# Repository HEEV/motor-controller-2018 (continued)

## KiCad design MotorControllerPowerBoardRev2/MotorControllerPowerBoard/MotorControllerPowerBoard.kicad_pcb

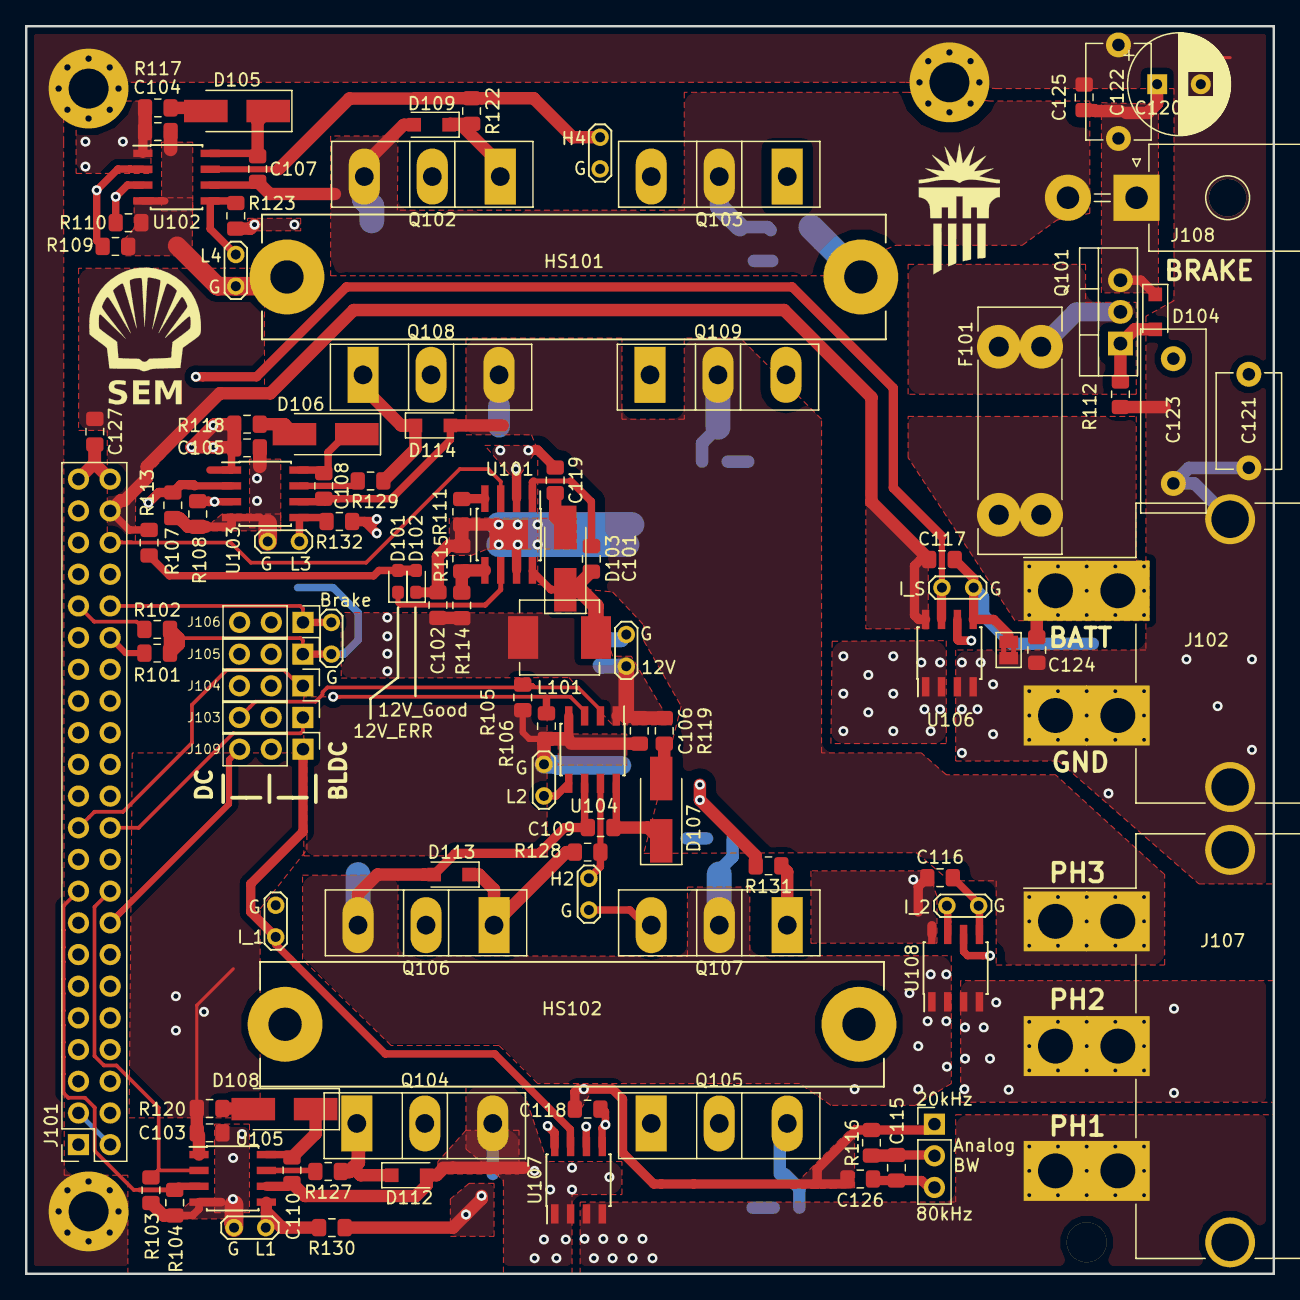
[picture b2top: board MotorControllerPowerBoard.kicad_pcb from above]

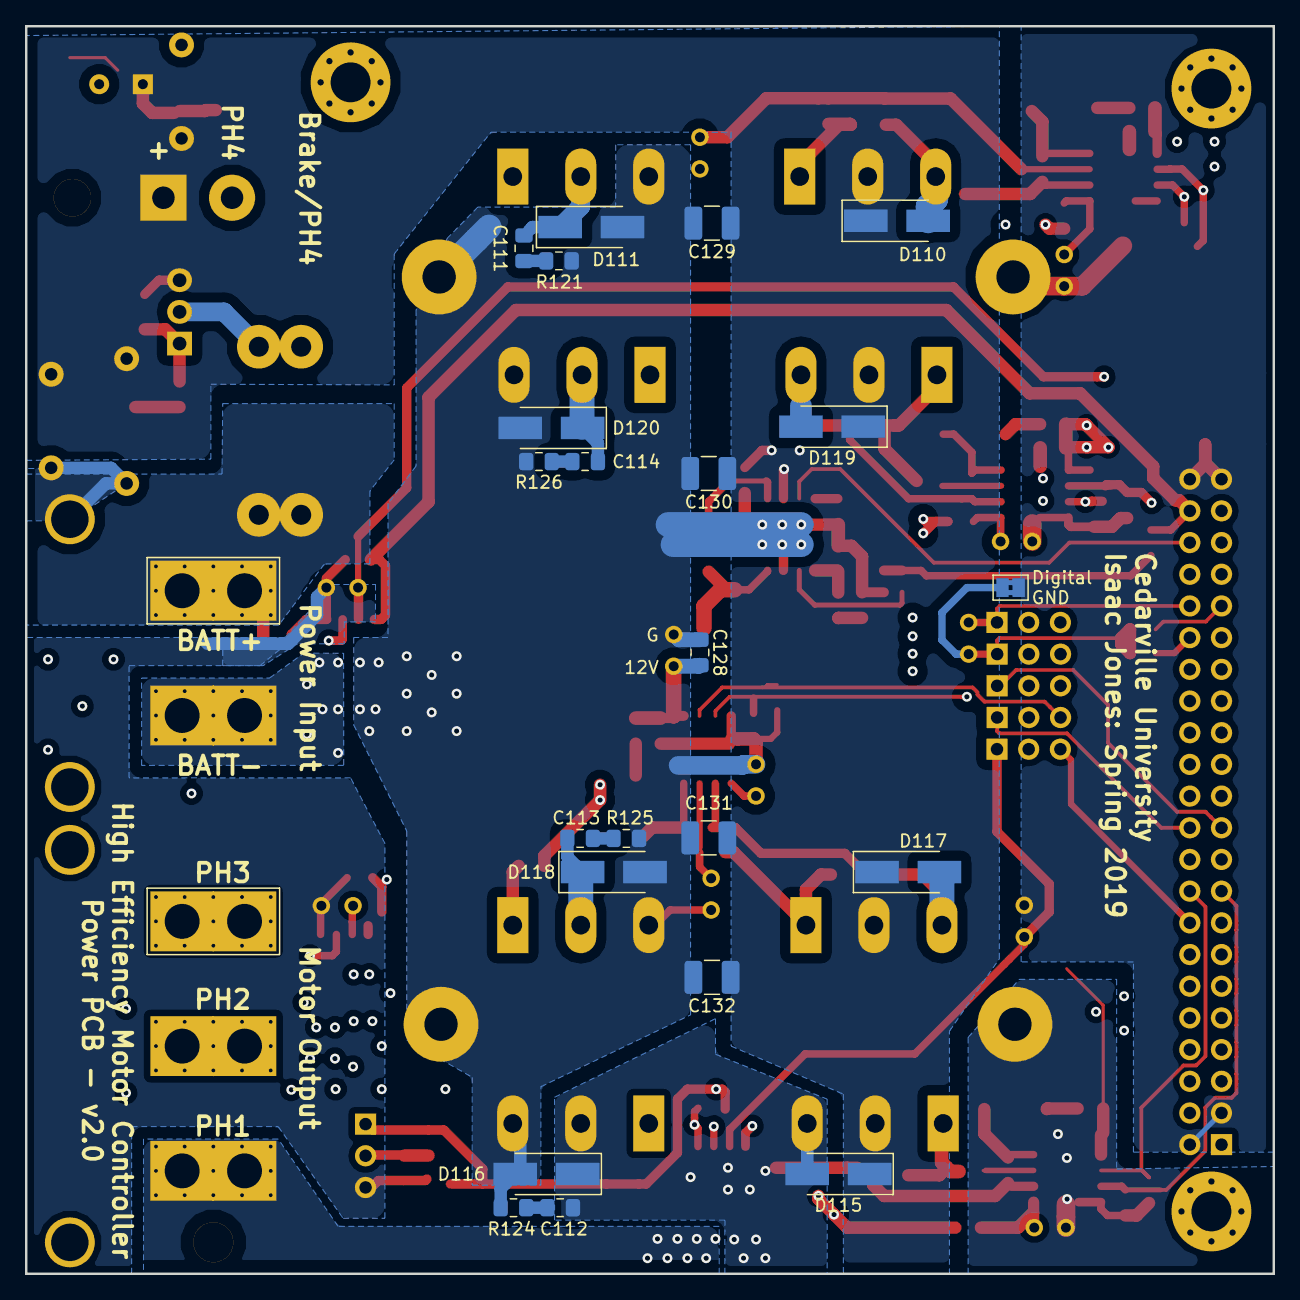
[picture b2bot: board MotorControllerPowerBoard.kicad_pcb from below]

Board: 4 copper layers, 100.0 x 100.0 mm, 130 parts (22 on the bottom side), 69 nets.

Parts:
C101: 0.1u/>16V; C_0805_2012Metric_Pad1.15x1.40mm_HandSolder
C102, C103, C104, C105, C106, C116, C117, C118, C119, C128: 1u; C_0805_2012Metric_Pad1.15x1.40mm_HandSolder
C107, C108, C109, C110: 0.1u; C_0805_2012Metric_Pad1.15x1.40mm_HandSolder
C111, C112, C113, C114: 10n; C_0805_2012Metric_Pad1.15x1.40mm_HandSolder
C115, C124, C125, C126, C127: opt; C_0805_2012Metric_Pad1.15x1.40mm_HandSolder
C120: opt; CP_Radial_D8.0mm_P3.50mm
C121, C122: opt; C_Disc_D7.5mm_W5.0mm_P7.50mm
C123: opt; C_Disc_D14.5mm_W5.0mm_P10.00mm
C129, C130, C131, C132: 4u7; C_1210_3225Metric_Pad1.42x2.65mm_HandSolder
D101: LED_RED; LED_0603_1608Metric_Pad1.05x0.95mm_HandSolder
D102: LED_GRN; LED_0603_1608Metric_Pad1.05x0.95mm_HandSolder
D103, D105, D106, D107, D108, D110, D111, D115, D116, D117, D118, D119, D120: SK56A; D_SMA_Handsoldering
D104, D109, D112, D113, D114: Zener_15V; D_SOD-123F
F101: Fuse/Bypass; Keystone_Blade_Fuseholder_3557-2
GNDPWR: MountingHole_3.2mm_M3
GNDPWR#2: MountingHole_3.2mm_M3_Pad_Via
HS101, HS102: CR401; Heatsink_CR401x50
J101: Trinamic Bridge; PinSocket_2x22_P2.54mm_Vertical
J102: Battery; Molex_Mini-Fit_Sr_42820-22XX_1x02_P10.00mm_Horizontal_Therm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
J103: P3H; PinHeader_1x03_P2.54mm_Vertical
J104: P3L; PinHeader_1x03_P2.54mm_Vertical
J105: P4H; PinHeader_1x03_P2.54mm_Vertical
J106: P4L; PinHeader_1x03_P2.54mm_Vertical
J107: Motor_BLDC; Molex_Mini-Fit_Sr_42820-32XX_1x03_P10.00mm_Horizontal_Therm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
J108: Brake; Molex_Mega-Fit_76825-0002_2x01_P5.70mm_Horizontal
J109: I_Sel; PinHeader_1x03_P2.54mm_Vertical
J110: BW_SEL; PinHeader_1x03_P2.54mm_Vertical
JP101, JP102: Jumper_NC_Small; SolderJumper-2_P1.3mm_Bridged2Bar_Pad1.0x1.5mm
L101: ETQP3M220KVN; PCC-M0630M-LP
Q101: SUP90P06-09L; TO-220-3_Vertical
Q102, Q103, Q104, Q105, Q106, Q107, Q108, Q109: IRFP3306; TO-247-3_Vertical
R101, R102, R103, R104, R105, R106, R107, R108, R109, R110, R112, R115, R116: 10k; R_0805_2012Metric_Pad1.15x1.40mm_HandSolder
R111: 22k; R_0805_2012Metric_Pad1.15x1.40mm_HandSolder
R113: 1k5; R_0805_2012Metric_Pad1.15x1.40mm_HandSolder
R114: 150k; R_0805_2012Metric_Pad1.15x1.40mm_HandSolder
R117: small; R_0805_2012Metric_Pad1.15x1.40mm_HandSolder
R118, R119, R120, R122, R123, R127, R128, R129, R130, R131, R132: R; R_0805_2012Metric_Pad1.15x1.40mm_HandSolder
R121, R124, R125, R126: 1R; R_0805_2012Metric_Pad1.15x1.40mm_HandSolder
TP101: LS1; TestPoint_2Pads_Pitch2.54mm_Drill0.8mm
TP102: I_SUM; TestPoint_2Pads_Pitch2.54mm_Drill0.8mm
TP103: LS2; TestPoint_2Pads_Pitch2.54mm_Drill0.8mm
TP104: I_PH1; TestPoint_2Pads_Pitch2.54mm_Drill0.8mm
TP105: LS3; TestPoint_2Pads_Pitch2.54mm_Drill0.8mm
TP106: LS4; TestPoint_2Pads_Pitch2.54mm_Drill0.8mm
TP107: I_PH2; TestPoint_2Pads_Pitch2.54mm_Drill0.8mm
TP110: V_BUCK; TestPoint_2Pads_Pitch2.54mm_Drill0.8mm
TP111: HS2; TestPoint_2Pads_Pitch2.54mm_Drill0.8mm
TP113: BRAKE; TestPoint_2Pads_Pitch2.54mm_Drill0.8mm
TP114: HS4; TestPoint_2Pads_Pitch2.54mm_Drill0.8mm
U101: LMR16020; SOIC-8-PowerPAD
U102, U103, U104, U105: LM5109; SOIC-8_3.9x4.9mm_P1.27mm
U106, U107, U108: ACS723xLCTR-20AB; SOIC-8_3.9x4.9mm_P1.27mm

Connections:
+5V: C116.1, C117.1, C118.1, C126.1, C127.1, J101.42, J110.1, R113.1, R116.2, U106.8, U107.8, U108.8
+BATT: C119.1, C120.1, C121.1, C122.1, C123.1, C125.1, C129.1, C130.1, C131.1, C132.1, D104.1, D110.1, D115.1, D117.1, D119.1, J101.1, J108.1, Q101.3, Q102.2, Q104.2, Q106.2, Q108.2, U101.2
/ADC_I_Ph_1: J101.15, J109.2
/ADC_I_Ph_2: J101.14, TP107.1, U108.7
/ADC_I_Sum: J101.16, J109.3, TP102.1, U106.7
/BH1: J101.18, J105.3, R103.1, U105.2
/BH2: J101.20, J103.3, R105.1, U104.2
/BH3: J103.2, R107.1, U103.2
/BH4: J105.2, R109.1, U102.2
/BL1: J101.17, J106.3, R104.1, U105.3
/BL2: J101.19, J104.3, R106.1, U104.3
/BL3: J104.2, R108.1, U103.3
/BL4: J106.2, R110.1, U102.3
/BRAKE: J101.36, J106.1, TP113.1
/BW_SEL: C115.1, J110.2, R116.1, U106.6, U107.6, U108.6
/ENABLE: J101.40, U101.3
/HS1: R127.2, U105.7
/HS2: R128.2, TP111.1, U104.7
/HS3: R129.2, U103.7
/HS4: R122.2, TP114.1, U102.7
/I_Ph_1: J109.1, TP104.1, U107.7
/LS1: R130.2, TP101.1, U105.5
/LS2: R131.2, TP103.1, U104.5
/LS3: R132.2, TP105.1, U103.5
/LS4: R123.2, TP106.1, U102.5
/MOTOR_PH1: J107.3, U107.3, U107.4
/MOTOR_PH2: J107.2, U108.3, U108.4
/MOTOR_PH3: C108.1, C114.1, D114.2, D119.2, D120.1, J107.1, Q108.3, Q109.2, U103.6
/MOTOR_PH4: C107.1, C111.1, D109.2, D110.2, D111.1, J108.2, Q102.3, Q103.2, U102.6
/P3H_in: J101.22, J103.1
/P3L_in: J101.21, J104.1
/PH1: C110.1, C112.1, D112.2, D115.2, D116.1, Q104.3, Q105.2, U105.6, U107.1, U107.2
/PH2: C109.2, C113.1, D113.2, D117.2, D118.1, Q106.3, Q107.2, U104.6, U108.1, U108.2
/PWM_H_IDLE: J101.34, R101.1
/PWM_L_IDLE: J101.35, R102.1
/P_GOOD: D101.1, U101.6
/V_BUCK: C102.1, C103.1, C104.1, C105.1, C106.1, C128.1, L101.2, R114.1, R117.2, R118.2, R119.2, R120.2, TP110.1, U102.1, U103.1, U104.1, U105.1
/V_IN: C124.1, F101.2, J102.1
GNDA: C115.2, C116.2, C117.2, C118.2, C126.2, C127.2, J101.2, J101.3, J101.43, J101.44, J110.3, JP101.2, JP102.1, TP102.2, TP104.2, TP107.2, U106.5, U107.5, U108.5
GNDD: J105.1, JP102.2, R101.2, R102.2, TP113.2
GNDMOS: C102.2, C103.2, C104.2, C105.2, C106.2, C119.2, C128.2, C129.2, C130.2, C131.2, C132.2, D102.1, D103.2, D111.2, D116.2, D118.2, D120.2, HS101.1, HS102.1, Q103.3, Q105.3, Q107.3, Q109.3, R103.2, R104.2, R105.2, R106.2, R107.2, R108.2, R109.2, R110.2, R111.2, R115.2, R121.2, R124.2, R125.2, R126.2, TP101.2, TP103.2, TP105.2, TP106.2, TP110.2, TP111.2, TP114.2, U101.0, U101.7, U102.4, U103.4, U104.4, U105.4, U106.1, U106.2
GNDPWR: C120.2, C121.2, C122.2, C123.2, C124.2, C125.2, GNDPWR#2.1, J102.0, J102.2, J107.0, J108.0, JP101.1, R112.2, U106.3, U106.4
unnamed: C101.1, D103.1, L101.1, U101.8
unnamed: C101.2, U101.1
unnamed: C107.2, D105.1, U102.8
unnamed: C108.2, D106.1, U103.8
unnamed: C109.1, D107.1, U104.8
unnamed: C110.2, D108.1, U105.8
unnamed: C111.2, R121.1
unnamed: C112.2, R124.1
unnamed: C113.2, R125.1
unnamed: C114.2, R126.1
unnamed: D101.2, D102.2, R113.2
unnamed: D104.2, Q101.1, R112.1
unnamed: D105.2, R117.1
unnamed: D106.2, R118.1
unnamed: D107.2, R119.1
unnamed: D108.2, R120.1
unnamed: D109.1, Q102.1, R122.1
unnamed: D112.1, Q104.1, R127.1
unnamed: D113.1, Q106.1, R128.1
unnamed: D114.1, Q108.1, R129.1
unnamed: F101.1, Q101.2
unnamed: Q103.1, R123.1
unnamed: Q105.1, R130.1
unnamed: Q107.1, R131.1
unnamed: Q109.1, R132.1
unnamed: R111.1, U101.4
unnamed: R114.2, R115.1, U101.5

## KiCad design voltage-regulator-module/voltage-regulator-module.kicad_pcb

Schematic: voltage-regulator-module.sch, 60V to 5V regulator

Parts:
C1: 4u7; C_1210_3225Metric
C2, C3: 100n; C_0805_2012Metric
C4: 10u; CP_Elec_6.3x5.8
C5: 4.7u; C_0805_2012Metric
C6: 1u; C_0805_2012Metric
D1: D_Schottky_Small_ALT; D_SMA
J1: Power; PinHeader_1x04_P2.54mm_Vertical
L1: 22u; PCC-M0630M-LP
R1: 10K; R_0805_2012Metric
R2: 33K; R_0805_2012Metric
R3: 68K; R_0805_2012Metric
R4: 12K; R_0805_2012Metric
U1: LMR16010; SOIC-8-PowerPAD

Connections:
/EN: J1.4, R1.2, U1.3 (ENABLE)
/Vin: C1.1, C2.1, J1.3, R1.1, U1.2 (VIN)
/Vout: C4.1, C5.1, C6.1, J1.1, L1.2, R3.1
GND: C1.2, C2.2, C4.2, C5.2, C6.2, D1.2, J1.2, R2.2, R4.2, U1.0 (PAD), U1.7 (GND)
unnamed: C3.1, D1.1, L1.1, U1.8 (SW)
unnamed: C3.2, U1.1 (BOOT)
unnamed: R2.1, U1.4 (RT/SYNC)
unnamed: R3.2, R4.1, U1.5 (FB)

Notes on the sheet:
Input capacitors rated for 100V
60V > Vin > 5V
Output: 5V, 1A

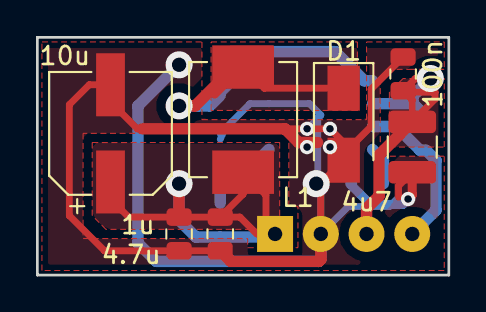
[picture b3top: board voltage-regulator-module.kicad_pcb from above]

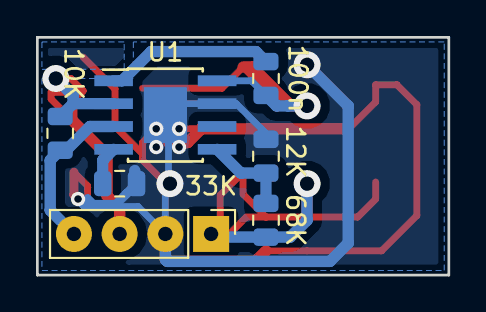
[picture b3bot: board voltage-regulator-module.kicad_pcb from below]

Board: 2 copper layers, 22.9 x 13.2 mm, 14 parts (7 on the bottom side), 8 nets.

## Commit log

2018-09-25 Added kicad-parts submodule
2018-09-25 initial commit of the schematics/block diagrams
2018-10-01 Added higherarchical pins to the Signal Processing block
2018-10-09 Added more signals to the top level diagram
2018-10-10 added parts library for all non-user-defined parts and symbols used in project
2018-10-10 added more signals and parts
2018-11-13 Changed hierarchy Added input protection circuitry
2018-11-13 Finished Input Protection Added annotations to the title block
2018-11-16 Microcontroller.sch: - Added many labels to pins - Bypass Capacitors - Crystal Oscilator - User Buttons and LEDs
2018-11-16 IO.sch: - Added more labels
2018-11-16 Other Files: - Stuff Changed
2018-11-16 Added new parts to cache lib
2018-11-17 sym-lib-table: Make library paths cross platform
2018-11-17 Added system library parts to project library Added a few more comments to IO.sch Added TMC4671 SPI bus as an output for microcontroller.sch Added some connections in the overview page Updated schema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
2018-11-20 stuff changed
2018-11-23 MotorControllerParts.lib: Added more parts
2018-11-23 power-supply.sch: Added some voltage regulators removed from main schematic
2018-11-23 microcontroller.sch: added some more outputs to the TMC4671 schematic
2018-11-23 TMC4671.sch: added a decoupling capacitors other base components
2018-11-23 motor-controller-hw.sch: Added power supply to the top level schematic Added connectors for all the IO pins
2018-11-23 IO.sch: page number changed
2018-11-23 fp-lib-table: changed library load order
2018-11-23 motor-controller-hw-cache.lib: library cache modifications
2018-11-23 sym-lib-table: changed library load order
2018-11-23 updated project schematics
2018-11-27 Moving away from TMC4671
2018-11-27 Added scmitt triggers to the input protection circuitry
2018-11-28 Voltage regualtor changes, name changes, and HANDS!!!
2018-11-28 Working schematics
2018-11-28 Compacted schematic layout
2018-11-28 Moved all parts into the MotorControllerParts.lib file
2018-11-28 Added footprints, changed pdf
2018-11-29 Finished adding footprints to the schematic, started layout
2018-11-30 Moved chaged order of op-amps to make PCB layout easier. More pcb part positioning
2018-11-30 Working PCB Layout
2018-11-30 Started routing
2018-12-01 PCB Routing
2018-12-04 Added mounting holes to pcb
2018-12-20 Adding BOM, changed some footprints -Changed footprints to linux models in schematics -Added field Digi-key# to all components -Started filling in said field
2018-12-22 Moved some parts into the project parts library messed with the PCB slightly
2018-12-22 Updated parts library
2018-12-22 Added all of the digi-key part numbers
2018-12-22 BOM stuff
2018-12-27 Fixed pad clearance issues
2019-01-15 added stuff
2019-01-18 Added a voltage regulator module PCB
2019-01-18 Updated parts library to latest commit
2019-03-31 PCB rev 1.1 -Fixed the TMC4671 footprint (use the Digi-Key layout) -Fixed the USB pull up issue for using the DFU bootloader -Fixed the orientation of the Hall sensor connector -Added a PTC on the ha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
2019-03-31 Update submodule
2019-04-30 some stuff changed
2019-04-30 I don't really know what happened here
2019-05-01 Power Stage Files Added
2019-05-01 Removed old pdfs
2019-05-02 Added more PDFs
2019-10-07 Update the PDF documents
2019-10-07 Update Kicad parts library
2019-10-07 Added design report, user guide, and readme
